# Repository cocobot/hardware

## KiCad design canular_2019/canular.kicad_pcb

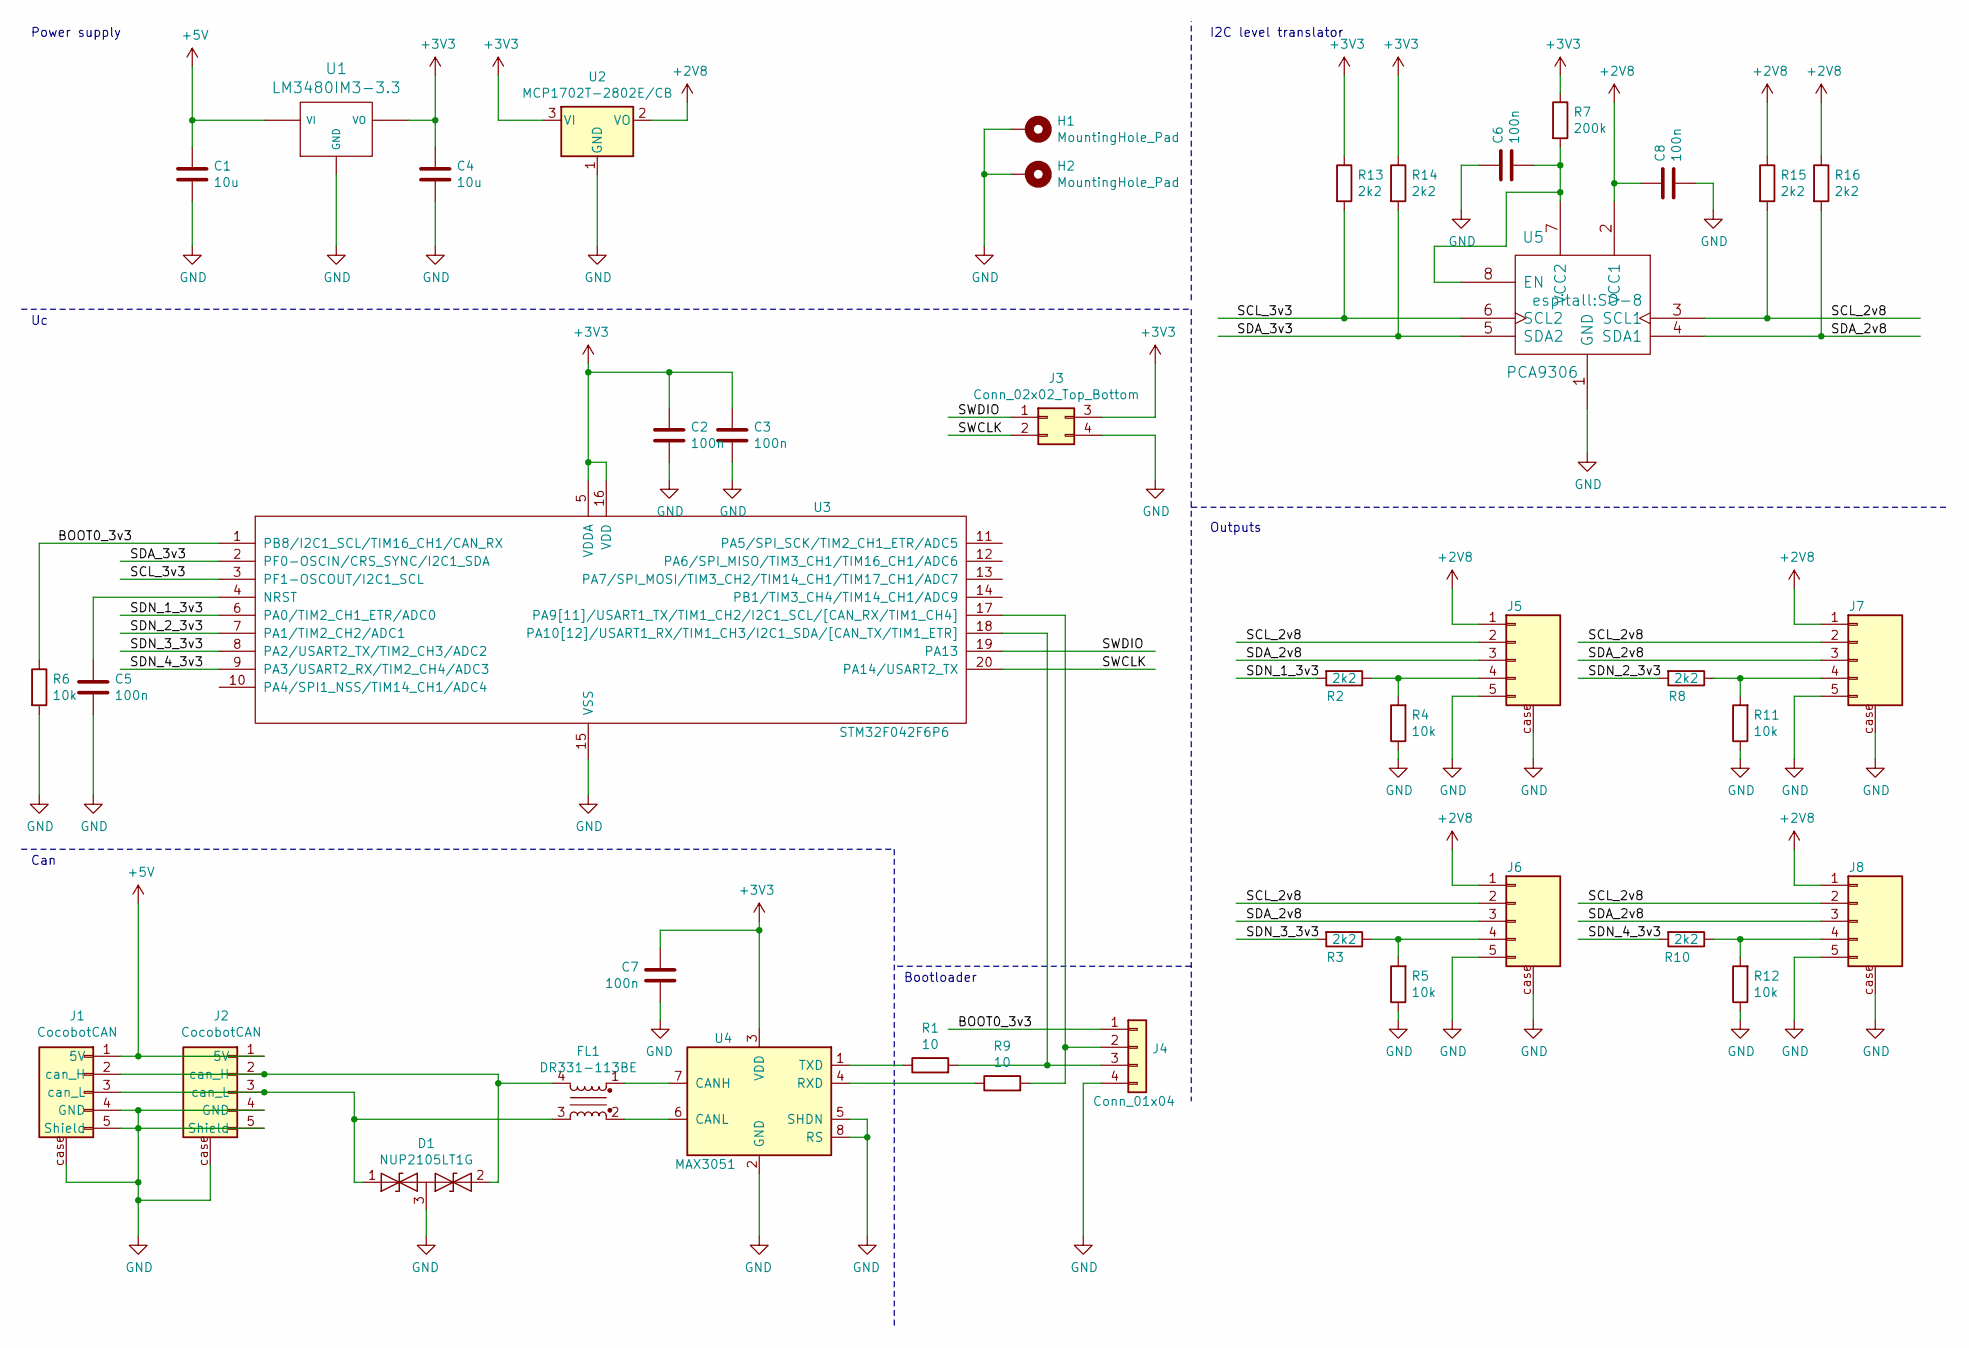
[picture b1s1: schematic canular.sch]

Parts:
C1, C4: 10u; C_0805
C2, C3, C5, C6, C7, C8: 100n; C_0603
D1: NUP2105LT1G; SOT-23
FL1: DR331-113BE; DR331
H1, H2: MountingHole_Pad; MountingHole_3.2mm_M3_Pad
J1, J2: CocobotCAN; JST_PH_S5B-PH-SM4-TB_05x2.00mm_Angled
J3: Conn_02x02_Top_Bottom; PinHeader_2x02_P2.54mm_Vertical
J4: Conn_01x04; PinHeader_1x04_P2.54mm_Vertical
J5, J6, J7, J8: JST_PH_S5B-PH-SM4-TB_05x2.00mm_Angled
R1, R9: 10; R_0603
R2, R3, R8, R10, R13, R14, R15, R16: 2k2; R_0603
R4, R5, R6, R11, R12: 10k; R_0603
R7: 200k; R_0603
U1: LM3480IM3-3.3; SOT-23
U2: MCP1702T-2802E/CB; SOT-23
U3: STM32F042F6P6; TSSOP-20_4.4x6.5mm_Pitch0.65mm
U4: MAX3051; SOIC-8_3.9x4.9mm_P1.27mm
U5: PCA9306; SO-8

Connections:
+2V8: C8.1, J5.1, J6.1, J7.1, J8.1, R15.1, R16.1, U2.2 (VO), U5.2 (VCC1)
+3V3: C2.1, C3.1, C4.1, C7.1, J3.3, R7.1, R13.1, R14.1, U1.1 (VO), U2.3 (VI), U3.5 (VDDA), U3.16 (VDD), U4.3 (VDD)
+5V: C1.1, J1.1 (5V), J2.1 (5V), U1.2 (VI)
/BOOT0_3v3: J4.1, R6.1, U3.1 (PB8/I2C1_SCL/TIM16_CH1/CAN_RX)
/SCL_2v8: J5.2, J6.2, J7.2, J8.2, R15.2, U5.3 (SCL1)
/SCL_3v3: R13.2, U3.3 (PF1-OSCOUT/I2C1_SCL), U5.6 (SCL2)
/SDA_2v8: J5.3, J6.3, J7.3, J8.3, R16.2, U5.4 (SDA1)
/SDA_3v3: R14.2, U3.2 (PF0-OSCIN/CRS_SYNC/I2C1_SDA), U5.5 (SDA2)
/SDN_1_3v3: R2.2, U3.6 (PA0/TIM2_CH1_ETR/ADC0)
/SDN_2_3v3: R8.2, U3.7 (PA1/TIM2_CH2/ADC1)
/SDN_3_3v3: R3.2, U3.8 (PA2/USART2_TX/TIM2_CH3/ADC2)
/SDN_4_3v3: R10.2, U3.9 (PA3/USART2_RX/TIM2_CH4/ADC3)
/SWCLK: J3.2, U3.20 (PA14/USART2_TX)
/SWDIO: J3.1, U3.19 (PA13)
GND: C1.2, C2.2, C3.2, C4.2, C5.2, C6.1, C7.2, C8.2, D1.3 (common), H1.1, H2.1, J1.4 (GND), J1.5 (Shield), J1.case, J2.4 (GND), J2.5 (Shield), J2.case, J3.4, J4.4, J5.5, J5.case, J6.5, J6.case, J7.5, J7.case, J8.5, J8.case, R4.1, R5.1, R6.2, R11.1, R12.1, U1.3 (GND), U2.1 (GND), U3.15 (VSS), U4.2 (GND), U4.5 (SHDN), U4.8 (RS), U5.1 (GND)
unnamed: C5.1, U3.4 (NRST)
unnamed: C6.2, R7.2, U5.7 (VCC2), U5.8 (EN)
unnamed: D1.1 (A1), FL1.3, J1.3 (can_L), J2.3 (can_L)
unnamed: D1.2 (A2), FL1.4, J1.2 (can_H), J2.2 (can_H)
unnamed: FL1.1, U4.7 (CANH)
unnamed: FL1.2, U4.6 (CANL)
unnamed: J4.2, R9.2, U3.17 (PA9[11]/USART1_TX/TIM1_CH2/I2C1_SCL/[CA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)
unnamed: J4.3, R1.2, U3.18 (PA10[12]/USART1_RX/TIM1_CH3/I2C1_SDA/[C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)
unnamed: J5.4, R2.1, R4.2
unnamed: J6.4, R3.1, R5.2
unnamed: J7.4, R8.1, R11.2
unnamed: J8.4, R10.1, R12.2
unnamed: R1.1, U4.1 (TXD)
unnamed: R9.1, U4.4 (RXD)

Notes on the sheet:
Power supply
Can
Bootloader
I2C level translator
Outputs

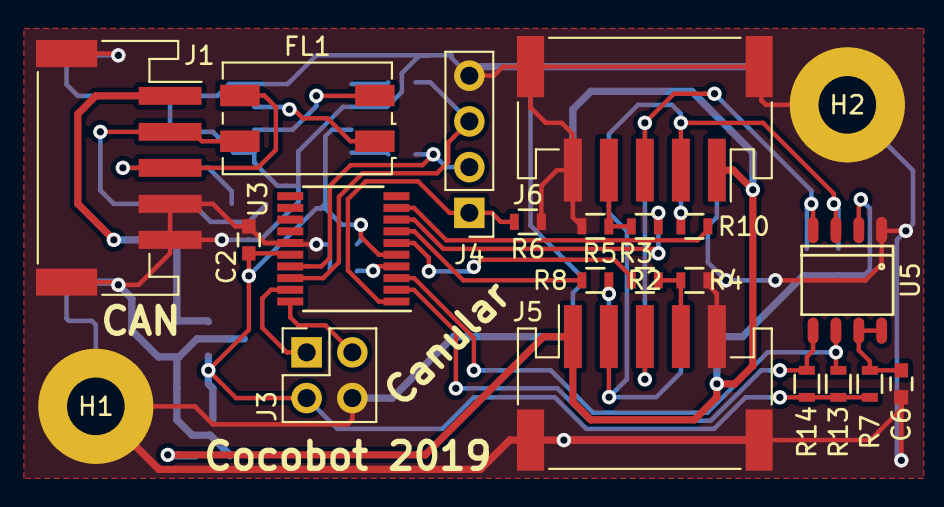
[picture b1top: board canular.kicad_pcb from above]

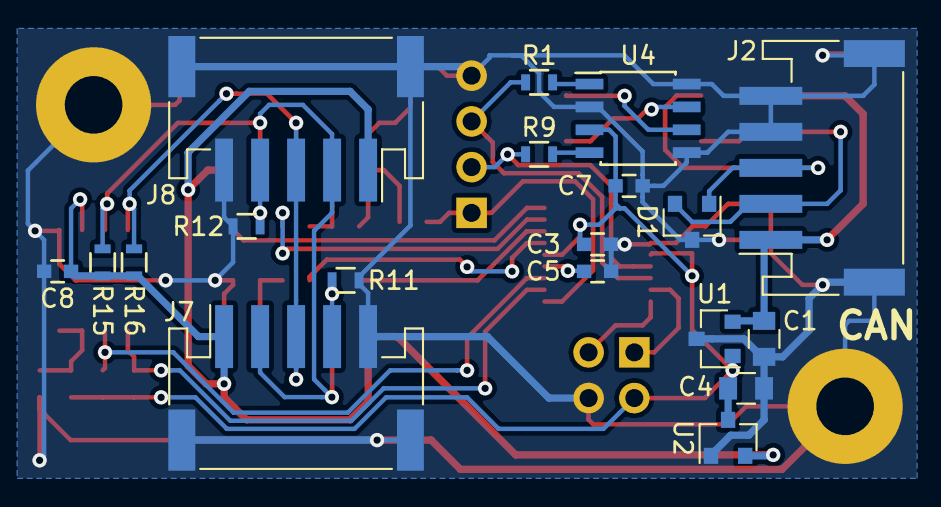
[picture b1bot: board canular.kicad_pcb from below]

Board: 2 copper layers, 41 parts (19 on the bottom side), 29 nets.

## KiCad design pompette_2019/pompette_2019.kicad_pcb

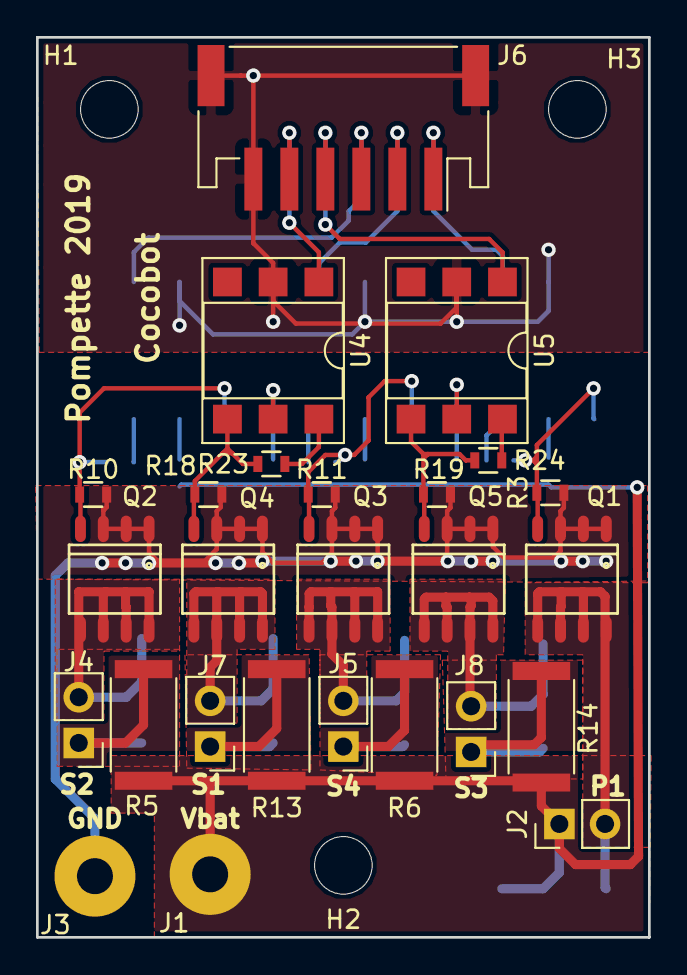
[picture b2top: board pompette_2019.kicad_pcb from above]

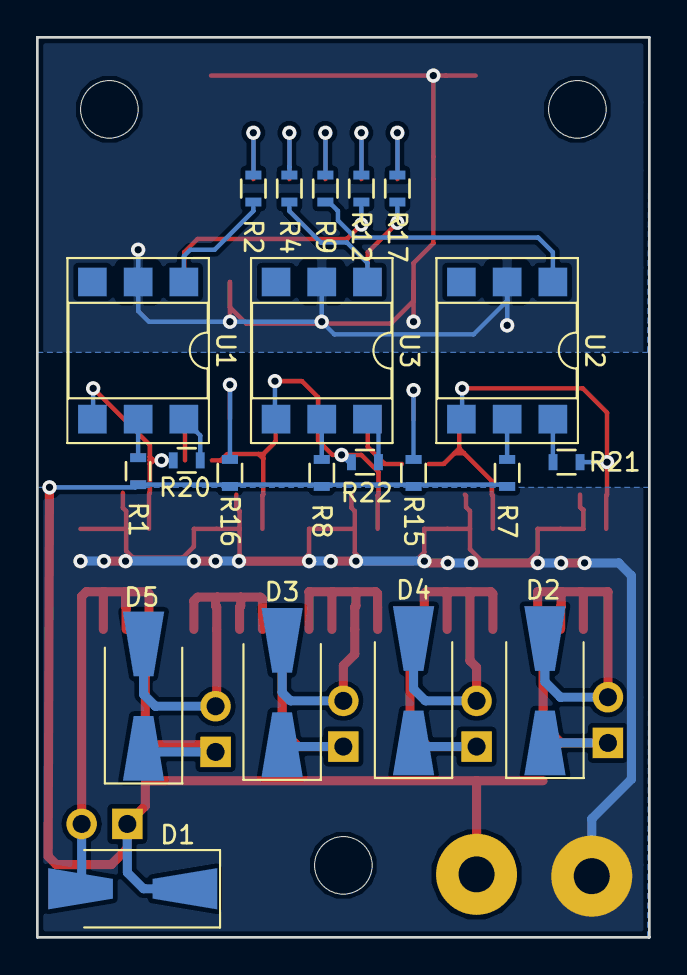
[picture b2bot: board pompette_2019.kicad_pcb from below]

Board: 2 copper layers, 34.0 x 50.0 mm, 50 parts (21 on the bottom side), 37 nets.

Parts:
D1, D2, D3, D4, D5: SS24; D_SMA-SMB_Universal_Handsoldering
H1, H2, H3: Conn_01x01; MountingHole_3.2mm_M3
J1, J3: Conn_01x01; SolderWirePad_single_2mmDrill
J2, J4, J5, J7, J8: Conn_01x02; Pin_Header_Straight_1x02_Pitch2.54mm
J6: JST_PH_S6B-PH-SM4-TB_06x2.00mm_Angled
Q1, Q2, Q3, Q4, Q5: DMG4466SSS-13
R1, R7, R8, R15, R16: 1k; R_0603
R2, R4, R9, R12, R17: 220; R_0603
R3, R10, R11, R18, R19: 10k; R_0603
R5, R6, R13, R14: R; R_2512
R20, R21, R22, R23, R24: 470k; R_0603
U1, U2, U3, U4, U5: CNY17-3-300E; DIP-6_W7.62mm_SMDSocket_SmallPads

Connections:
+BATT: D1.1, J1.1, J2.1, R1.1, R5.1, R6.1, R7.1, R8.1, R13.1, R14.1, R15.1, R16.1
/pump_3v3: J6.1, R2.2
/solenoid_1_3v3: J6.2, R4.2
/solenoid_2_3v3: J6.3, R9.2
/solenoid_3_3v3: J6.4, R12.2
/solenoid_4_3v3: J6.5, R17.2
GND: J3.1, Q1.S, Q2.S, Q3.S, Q4.S, Q5.S, R3.2, R10.2, R11.2, R18.2, R19.2
GNDD: J6.6, J6.case, U1.2, U2.2, U3.2, U4.2, U5.2
unnamed: D1.2, J2.2, Q1.D
unnamed: D2.1, J4.1, R5.2
unnamed: D2.2, J4.2, Q2.D
unnamed: D3.1, J5.1, R6.2
unnamed: D3.2, J5.2, Q3.D
unnamed: D4.1, J7.1, R13.2
unnamed: D4.2, J7.2, Q4.D
unnamed: D5.1, J8.1, R14.2
unnamed: D5.2, J8.2, Q5.D
unnamed: Q1.G, R3.1, R20.1, U1.4
unnamed: Q2.G, R10.1, R21.1, U2.4
unnamed: Q3.G, R11.1, R22.1, U3.4
unnamed: Q4.G, R18.1, R23.1, U4.4
unnamed: Q5.G, R19.1, R24.1, U5.4
unnamed: R1.2, U1.5
unnamed: R2.1, U1.1
unnamed: R4.1, U3.1
unnamed: R7.2, U2.5
unnamed: R8.2, U3.5
unnamed: R9.1, U2.1
unnamed: R12.1, U5.1
unnamed: R15.2, U4.5
unnamed: R16.2, U5.5
unnamed: R17.1, U4.1
unnamed: R20.2, U1.6
unnamed: R21.2, U2.6
unnamed: R22.2, U3.6
unnamed: R23.2, U4.6
unnamed: R24.2, U5.6

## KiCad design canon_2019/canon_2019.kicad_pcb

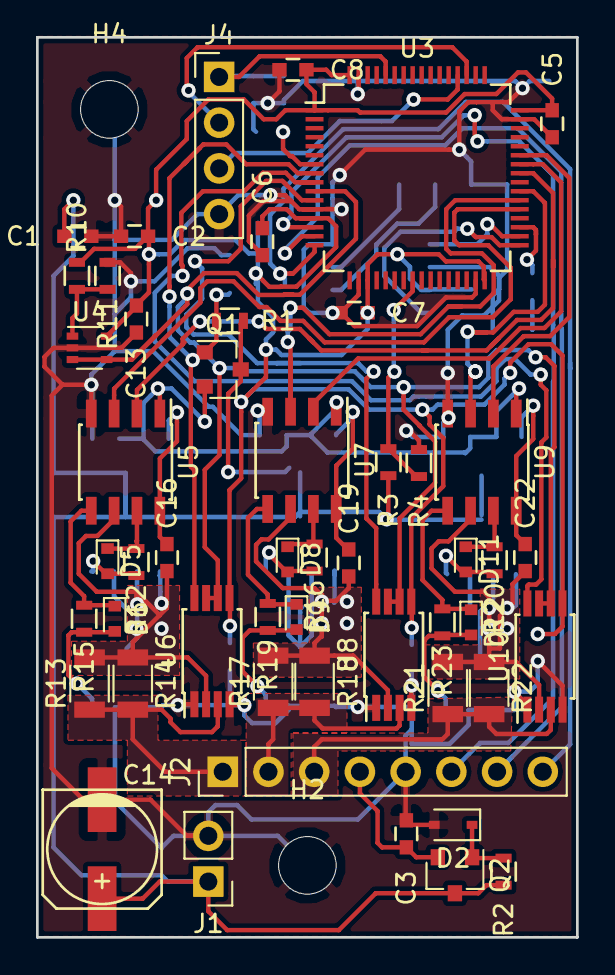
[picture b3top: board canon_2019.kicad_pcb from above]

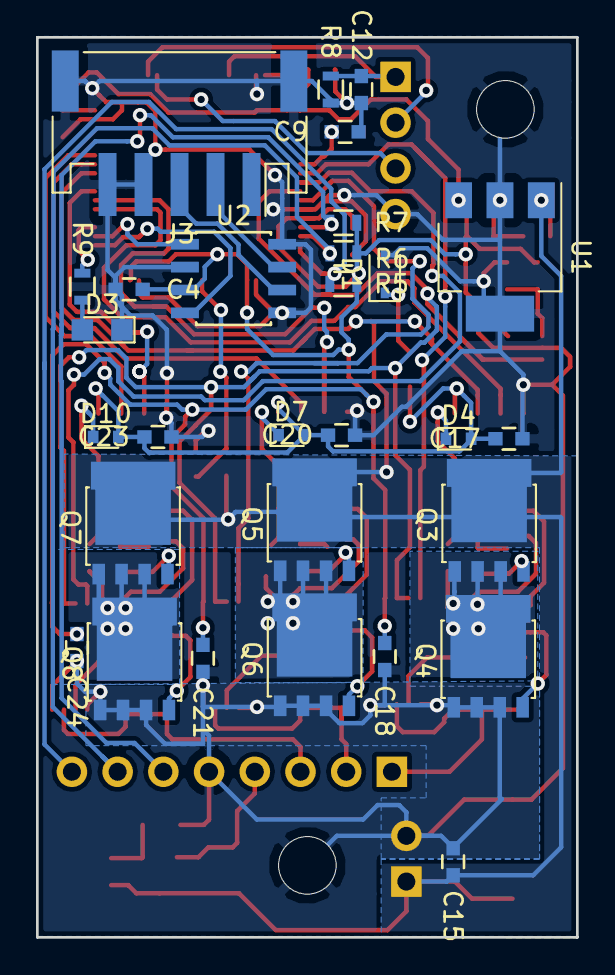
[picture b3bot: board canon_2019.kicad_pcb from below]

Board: 2 copper layers, 30.0 x 50.0 mm, 81 parts (29 on the bottom side), 53 nets.

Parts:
C1, C4, C5, C6, C7, C8, C9, C12, C13, C16, C17, C18, C19, C20, C21, C22, C23, C24: 100n; C_0603
C2, C3: 470n; C_0603
C14: CP; c_elec_6.3x7.7
C15: 2u2; C_0603
D1: BZD27Cxx/15V; D_SOD-323
D2: BZD27Cxx/5V6; D_SOD-323
D3: LED; LED_0805
D4, D5, D6, D7, D8, D9, D10, D11, D12: BAS-40-02V-V-G-08; D_SOD-523
H2, H4: MountingHole_Pad; MountingHole_3.2mm_M3
J1: Conn_01x02; Pin_Header_Straight_1x02_Pitch2.54mm
J2: Conn_01x08; Pin_Header_Straight_1x08_Pitch2.54mm
J3: CocobotCAN; JST_PH_S5B-PH-SM4-TB_05x2.00mm_Angled
J4: Conn_01x04; Pin_Header_Straight_1x04_Pitch2.54mm
Q1: BSS126; SOT-23
Q2: SO2222A; SOT-23
Q3, Q4, Q5, Q6, Q7, Q8: Q_NMOS_LFPAK; SOT-669_LFPAK
R1, R2, R3, R5, R6, R7, R8, R10, R11: 10k; R_0603
R4, R9: 1k; R_0603
R12, R15, R16, R19, R20, R23: 47; R_0603
R13, R14, R17, R18, R21, R22: 5m; R_1206
U1: LM3940IMP-3.3; SOT-223-3_TabPin2
U2: MAX3051; SOIC-8_3.9x4.9mm_Pitch1.27mm
U3: STM32L496RGTx; LQFP-64_10x10mm_Pitch0.5mm
U4: OPA349SA-3K; SOT-353_SC-70-5
U5, U7, U9: IR2104; SOIC-8_3.9x4.9mm_Pitch1.27mm
U6, U8, U10: INA240A1PW; TSSOP-8_4.4x3mm_Pitch0.65mm

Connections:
+3V3: C2.1, C4.1, C5.1, C6.1, C7.1, C8.1, C13.2, C18.2, C21.2, C24.2, R5.1, R6.1, R7.1, R10.1, U1.3, U2.3, U3.1, U3.13, U3.19, U3.32, U3.48, U3.64, U4.5, U6.5, U8.5, U10.5
/Control/BAT_ADC_0-3v3: R3.2, R4.1, U3.24
/Control/HALL_U_3v3: J2.6, R7.2, U3.14
/Control/HALL_V_3v3: J2.7, R6.2, U3.15
/Control/HALL_W_3v3: J2.8, R5.2, U3.16
/Control/I_U_0-3v3: U3.8, U6.8
/Control/I_V_0-3v3: U3.11, U8.8
/Control/I_W_0-3v3: U3.9, U10.8
/Control/REF_1v65: U3.10, U4.3, U4.4, U6.6, U6.7, U8.6, U8.7, U10.6, U10.7
/Control/UEN_3v3: U3.37, U5.3
/Control/UPWM_3v3: U3.41, U5.2
/Control/VEN_3v3: U3.38, U7.3
/Control/VPWM_3v3: U3.42, U7.2
/Control/WEN_3v3: U3.39, U9.3
/Control/WPWM_3v3: U3.43, U9.2
/Control/boot0_3v3: C12.1, J4.1, R8.1, U3.60
/Control/can_rx: U2.4, U3.33
/Control/can_tx: U2.1, U3.34
/Control/rx_3v3: J4.3, U3.52
/Control/tx_3v3: J4.2, U3.51
/Drive/U_PH: J2.1, R13.1, R14.2, U6.3
/Drive/V_PH: J2.2, R17.1, R18.2, U8.3
/Drive/Vdrv: C17.1, C20.1, C23.1, D4.2, D7.2, D10.2, Q1.2, U5.1, U7.1, U9.1
/Drive/W_PH: J2.3, R21.1, R22.2, U10.3
/PWR_BAT: C1.1, C14.1, C15.1, J1.1, Q1.3, Q2.3, Q3.5, Q5.5, Q7.5, R1.1, R2.1, R3.1, U1.1
GND: C1.2, C2.2, C3.2, C4.2, C5.2, C6.2, C7.2, C8.2, C9.2, C12.2, C13.1, C14.2, C15.2, C17.2, C18.1, C20.2, C21.1, C23.2, C24.1, D1.2, D2.2, D3.1, H2.1, H4.1, J1.2, J2.5, J3.4, J3.5, J3.case, J4.4, Q4.1, Q4.2, Q4.3, Q6.1, Q6.2, Q6.3, Q8.1, Q8.2, Q8.3, R4.2, R8.2, R11.2, U1.2, U2.2, U2.5, U2.8, U3.12, U3.18, U3.31, U3.47, U3.63, U4.2, U5.4, U6.1, U6.4, U7.4, U8.1, U8.4, U9.4, U10.1, U10.4
unnamed: C3.1, J2.4, Q2.2
unnamed: C9.1, U3.7
unnamed: C16.1, D4.1, U5.8
unnamed: C16.2, Q3.1, Q3.2, Q3.3, Q4.5, R13.2, R14.1, U5.6, U6.2
unnamed: C19.1, D7.1, U7.8
unnamed: C19.2, Q5.1, Q5.2, Q5.3, Q6.5, R17.2, R18.1, U7.6, U8.2
unnamed: C22.1, D10.1, U9.8
unnamed: C22.2, Q7.1, Q7.2, Q7.3, Q8.5, R21.2, R22.1, U9.6, U10.2
unnamed: D1.1, Q1.1, R1.2
unnamed: D2.1, Q2.1, R2.2
unnamed: D3.2, R9.2
unnamed: D5.1, R12.2, U5.7
unnamed: D5.2, Q3.4, R12.1
unnamed: D6.1, R15.2, U5.5
unnamed: D6.2, Q4.4, R15.1
unnamed: D8.1, R16.2, U7.7
unnamed: D8.2, Q5.4, R16.1
unnamed: D9.1, R19.2, U7.5
unnamed: D9.2, Q6.4, R19.1
unnamed: D11.1, R20.2, U9.7
unnamed: D11.2, Q7.4, R20.1
unnamed: D12.1, R23.2, U9.5
unnamed: D12.2, Q8.4, R23.1
unnamed: J3.2, U2.7
unnamed: J3.3, U2.6
unnamed: R9.1, U3.35
unnamed: R10.2, R11.1, U4.1

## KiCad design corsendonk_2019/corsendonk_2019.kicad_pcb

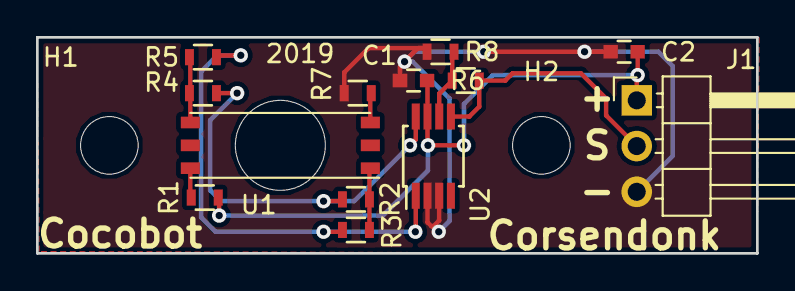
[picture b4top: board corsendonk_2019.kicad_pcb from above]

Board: 2 copper layers, 40.0 x 12.0 mm, 15 parts (0 on the bottom side), 10 nets.

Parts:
C1: 100n; C_0603
C2: 2u2; C_0603
H1, H2: Conn_01x01; MountingHole_3.2mm_M3
J1: Conn_01x03; Pin_Header_Angled_1x03_Pitch2.54mm
R1, R2, R3, R4, R5, R6, R7, R8: R; R_0603
U1: 2SMPP-02
U2: AD628; MSOP-8_3x3mm_Pitch0.65mm

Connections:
+5V: C1.2, C2.1, J1.1, R1.1, U2.7
/pres_0-5v: J1.2, R6.2, U2.5
GND: C1.1, C2.2, J1.3, R7.2, R8.1, U2.2, U2.3
unnamed: R1.2, U1.6
unnamed: R2.1, R4.1, U2.8
unnamed: R2.2, R3.2, U1.1
unnamed: R3.1, R5.1, U2.1
unnamed: R4.2, R5.2, U1.4
unnamed: R6.1, R8.2, U2.6
unnamed: R7.1, U1.3

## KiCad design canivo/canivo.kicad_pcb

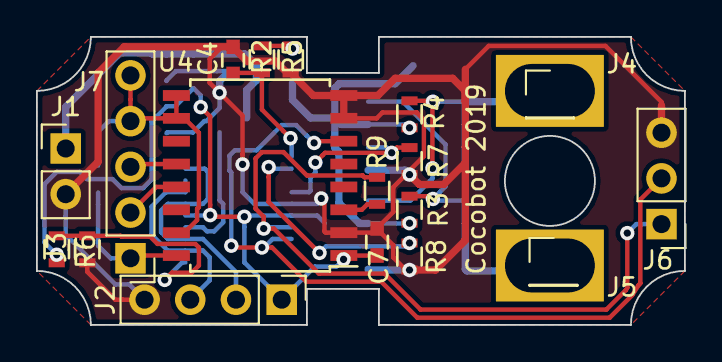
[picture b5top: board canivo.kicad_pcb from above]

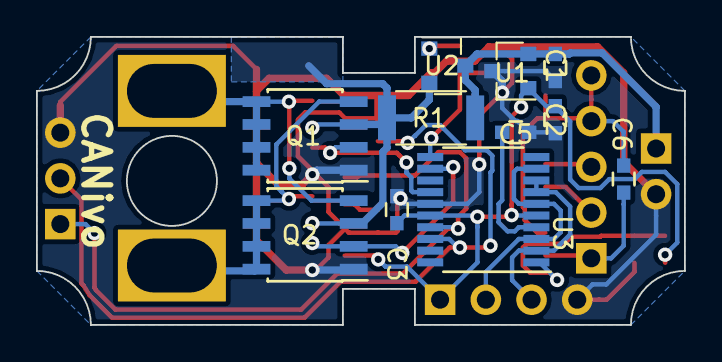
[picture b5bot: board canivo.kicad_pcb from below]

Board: 2 copper layers, 36.0 x 16.0 mm, 29 parts (11 on the bottom side), 21 nets.

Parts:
C1, C2, C3, C4, C5, C6, C7: 100n; C_0603
J1: Conn_01x02; Pin_Header_Straight_1x02_Pitch2.54mm
J2: Conn_01x04; Pin_Header_Straight_1x04_Pitch2.54mm
J3: Conn_01x02; R_0603
J4, J5: Conn_01x01; Pin_Header_Straight_1x01_Pitch2.54mm
J6: Conn_01x03; Pin_Header_Straight_1x03_Pitch2.54mm
J7: Conn_01x05; Pin_Header_Straight_1x05_Pitch2.54mm
Q1, Q2: DMC3025LSD; SOIC-8_3.9x4.9mm_Pitch1.27mm
R1: 0.05; R_2010
R2, R5: 1k; R_0603
R3, R4, R7, R8: 100k; R_0603
R6: 10k; R_0603
R9: 10; R_0603
U1: LM3480IM3-3.3; SOT-23
U2: ZXCT1009FTA; SOT-23
U3: STM32F042F6P6; TSSOP-20_4.4x6.5mm_Pitch0.65mm
U4: ISO1050DW; SOIC-16W_7.5x10.3mm_Pitch1.27mm

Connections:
+3V3: C2.1, C3.1, C7.1, J2.1, J3.1, U1.1, U3.5, U3.16, U4.1
+5P: C1.1, J1.1, R1.1, U1.2, U2.3
GND: C1.2, C2.2, C3.2, C4.2, C5.2, C7.2, J1.2, J2.4, J6.3, Q1.1, Q2.1, R5.2, R6.2, R7.2, R8.2, U1.3, U3.15, U4.2, U4.7, U4.8
unnamed: C4.1, R2.2, U3.11
unnamed: C5.1, U3.4
unnamed: C6.1, J7.1, U4.16
unnamed: C6.2, J7.4, J7.5, U4.9, U4.10, U4.15
unnamed: Q1.3, Q2.3, R1.2, R3.1, R4.1, U2.2
unnamed: J4.1, Q1.5, Q1.6, Q1.7, Q1.8, Q2.4, R4.2
unnamed: J5.1, Q1.4, Q2.5, Q2.6, Q2.7, Q2.8, R3.2
unnamed: J2.2, U3.3, U3.6, U3.9
unnamed: J2.3, U3.2, U3.7, U3.8
unnamed: J3.2, R6.1, U3.1
unnamed: J6.1, R9.2, U3.17
unnamed: J6.2, U3.18, U4.6
unnamed: J7.2, U4.13
unnamed: J7.3, U4.12
unnamed: Q1.2, R7.1, U3.14
unnamed: Q2.2, R8.1, U3.12
unnamed: R2.1, R5.1, U2.1
unnamed: R9.1, U4.3

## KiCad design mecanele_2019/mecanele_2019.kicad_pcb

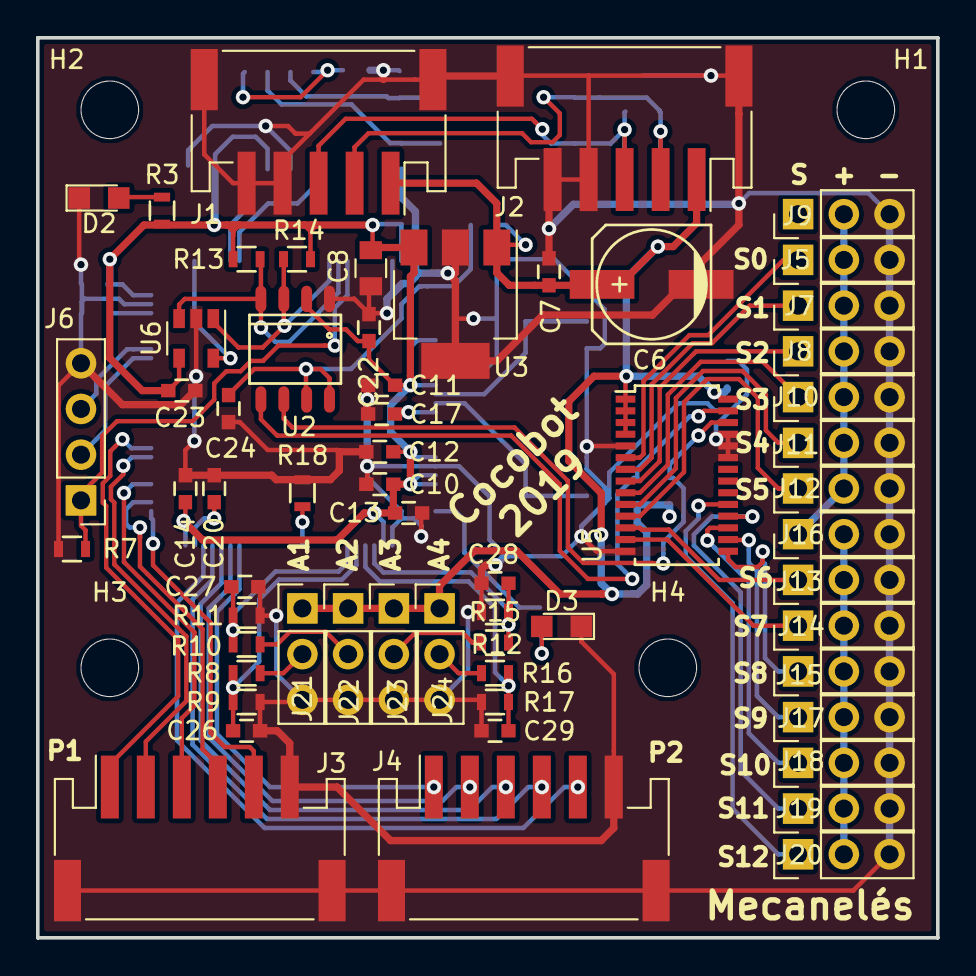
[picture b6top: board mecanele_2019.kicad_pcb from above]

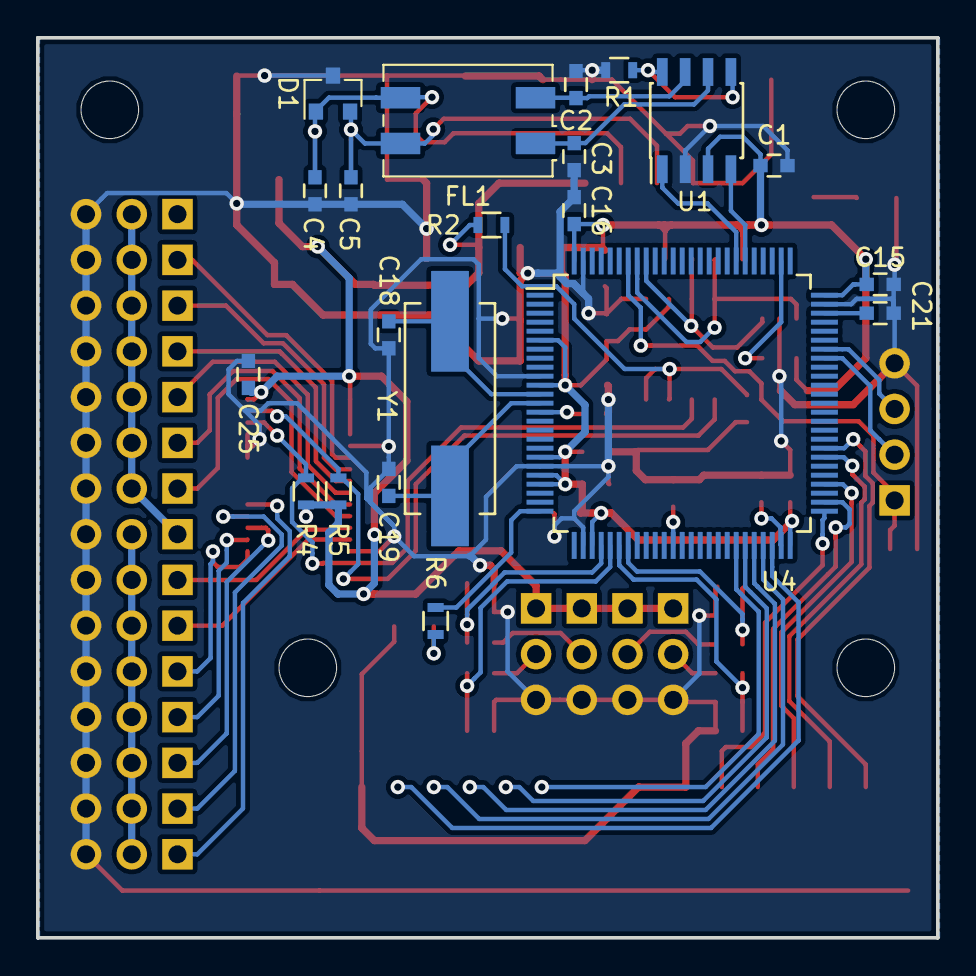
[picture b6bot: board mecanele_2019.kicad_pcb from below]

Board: 2 copper layers, 50.0 x 50.0 mm, 85 parts (21 on the bottom side), 61 nets.

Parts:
C1, C10, C11, C12, C13, C14, C15, C16, C17, C22, C23, C24, C25, C26, C27, C28, C29: 100n; C_0603
C2, C3, C4, C5: C; C_0603
C6: CP; c_elec_6.3x7.7
C7, C20, C21: 2u2; C_0603
C8: 47u; C_0805
C18, C19: 20p; C_0603
D1: NUP2105LT1G; SOT-23
D2, D3: LED; LED_0805
FL1: DR331-113BE; DR331
H1, H2, H3, H4: Conn_01x01; MountingHole_3.2mm_M3
J1, J2: CocobotCAN; JST_PH_S5B-PH-SM4-TB_05x2.00mm_Angled
J3, J4: JST_PH_S6B-PH-SM4-TB_06x2.00mm_Angled
J5, J7, J8, J9, J10, J11, J12, J13, J14, J15, J16, J17, J18, J19, J20, J21, J22, J23, J24: Conn_01x03; Pin_Header_Straight_1x03_Pitch2.54mm
J6: Conn_01x04; Socket_Strip_Straight_1x04_Pitch2.54mm
R1: 0; R_0603
R2: 200k; R_0603
R3, R6: 220; R_0603
R4, R5, R13, R14: 2k2; R_0603
R7, R18: 10k; R_0603
R8, R9, R10, R11, R12, R15, R16, R17: R; R_0603
U1: MAX3051ESA; SOIC-8_3.9x4.9mm_Pitch1.27mm
U2: PCA9306; SO-8
U3: LM3940IMP-3.3; SOT-223-3_TabPin2
U4: STM32F407VG; LQFP-100_14x14mm_Pitch0.5mm
U5: PCA9685; TSSOP-28_4.4x9.7mm_Pitch0.65mm
U6: 24LC64T-I; SOT-23-5
Y1: 8M; Crystal_HC49-SD_SMD

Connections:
+3V3: C1.1, C8.1, C10.1, C11.1, C12.1, C13.1, C14.1, C15.1, C16.1, C22.1, C23.1, R3.1, R13.1, R14.1, U1.3, U2.2, U3.3, U4.6, U4.11, U4.19, U4.21, U4.22, U4.28, U4.50, U4.75, U4.100, U6.4
+5V: C6.1, C7.1, C25.1, J1.1, J2.1, J21.1, J22.1, J23.1, J24.1, R2.1, R4.1, R5.1, U3.1, U5.1, U5.2, U5.3, U5.4, U5.28
/CAN/can_rx_3v3: U1.4, U4.81
/CAN/can_tx_3v3: U1.1, U4.82
/Sensor/ana_1_0-3v3: C26.1, R8.2, R9.2, U4.31
/Sensor/ana_2_0-3v3: C27.1, R10.2, R11.2, U4.32
/Sensor/ana_3_0-3v3: C28.1, R12.2, R15.2, U4.29
/Sensor/ana_4_0-3v3: C29.1, R16.2, R17.2, U4.30
/Servo/S0: J5.1, U5.6
/Servo/S1: J7.1, U5.7
/Servo/S2: J8.1, U5.8
/Servo/S3: J10.1, U5.9
/Servo/S4: J11.1, U5.10
/Servo/S5: J12.1, U5.11
/Servo/S6: J13.1, U5.12
/Servo/S7: J14.1, U5.13
/Servo/S8: J15.1, U5.15
/Servo/S9: J17.1, U5.16
/Servo/S10: J18.1, U5.17
/Servo/S11: J19.1, U5.18
/Servo/S12: J20.1, U5.19
/Servo/scl_3v3: R14.2, U2.3, U4.92, U6.1
/Servo/sda_3v3: R13.2, U2.4, U4.93, U6.3
/uc/BOOT0_3v3: J6.1, R7.1, U4.94
/uc/BOOT1_3v3: R18.1, U4.37
/uc/nSRST_3v3: C17.1, U4.14
/uc/pump_1_3v3: J3.1, U4.58
/uc/pump_2_3v3: J4.1, U4.44
/uc/solenoid_1_3v3: J3.2, U4.57
/uc/solenoid_2_3v3: J3.3, U4.54
/uc/solenoid_3_3v3: J3.4, U4.52
/uc/solenoid_4_3v3: J3.5, U4.51
/uc/solenoid_5_3v3: J4.2, U4.45
/uc/solenoid_6_3v3: J4.3, U4.46
/uc/solenoid_7_3v3: J4.4, U4.47
/uc/solenoid_8_3v3: J4.5, U4.48
GND: C1.2, C2.2, C3.2, C4.2, C5.2, C6.2, C7.2, C8.2, C10.2, C11.2, C12.2, C13.2, C14.2, C15.2, C16.2, C17.2, C18.2, C19.2, C20.2, C21.2, C22.2, C23.2, C24.2, C25.2, C26.2, C27.2, C28.2, C29.2, D1.3, D2.1, D3.1, J1.4, J1.5, J1.case, J2.4, J2.5, J2.case, J3.6, J3.case, J4.6, J4.case, J5.3, J6.4, J7.3, J8.3, J9.3, J10.3, J11.3, J12.3, J13.3, J14.3, J15.3, J16.3, J17.3, J18.3, J19.3, J20.3, J21.3, J22.3, J23.3, J24.3, R1.2, R7.2, R9.1, R11.1, R15.1, R17.1, R18.2, U1.2, U2.1, U3.2, U4.10, U4.20, U4.27, U4.74, U4.99, U5.5, U5.14, U5.23, U5.24, U5.25, U6.2
unnamed: C2.1, FL1.2, U1.7
unnamed: C3.1, FL1.1, U1.6
unnamed: C4.1, D1.1, FL1.3, J1.2, J2.2
unnamed: C5.1, D1.2, FL1.4, J1.3, J2.3
unnamed: C18.1, U4.12, Y1.1
unnamed: C19.1, U4.13, Y1.2
unnamed: C20.1, U4.49
unnamed: C21.1, U4.73
unnamed: C24.1, R2.2, U2.7, U2.8
unnamed: D2.2, R3.2
unnamed: D3.2, R6.2
unnamed: J6.2, U4.68
unnamed: J6.3, U4.69
unnamed: J5.2, J7.2, J8.2, J9.2, J10.2, J11.2, J12.2, J16.1
unnamed: J13.2, J14.2, J15.2, J16.2, J17.2, J18.2, J19.2, J20.2
unnamed: J21.2, R8.1
unnamed: J22.2, R10.1
unnamed: J23.2, R12.1
unnamed: J24.2, R16.1
unnamed: R1.1, U1.5, U1.8
unnamed: R4.2, U2.6, U5.26
unnamed: R5.2, U2.5, U5.27
unnamed: R6.1, U4.25
unnamed: U4.77, U6.5

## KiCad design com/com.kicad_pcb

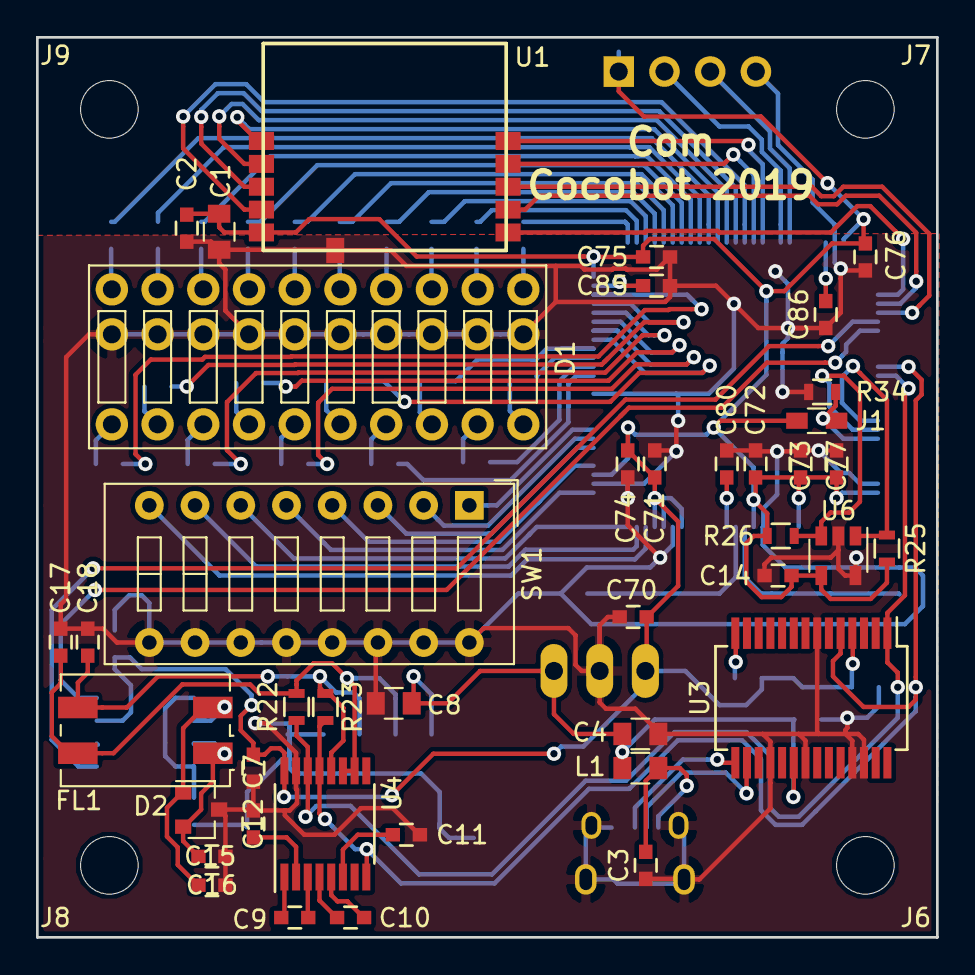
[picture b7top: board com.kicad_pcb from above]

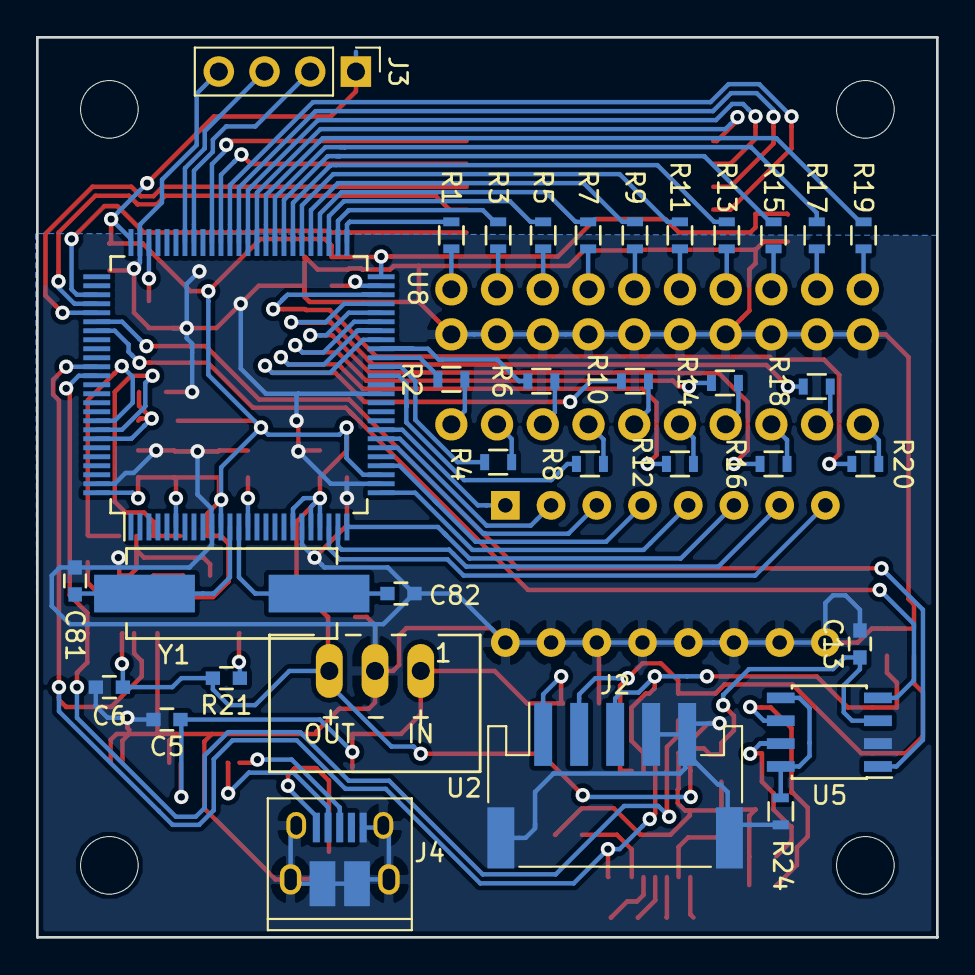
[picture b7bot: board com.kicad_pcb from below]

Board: 2 copper layers, 50.0 x 50.0 mm, 79 parts (34 on the bottom side), 89 nets.

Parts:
C1, C8: 10u; C_0805
C2, C5, C6, C7, C9, C10, C11, C12, C13, C14, C71, C72, C73, C74, C75, C76, C77, C80: 100n; C_0603
C3: 10n; C_0603
C4: 4u7; C_0805
C15, C16, C17, C18: C; C_0603
C70: 10u; C_0603
C81, C82: 20p; C_0603
C85, C86: 2u2; C_0603
D1: XGURUGX10D
D2: NUP2105LT1G; SOT-23
FL1: DR331-113BE; DR331
J1: Conn_01x02; R_0603_HandSoldering
J2: CocobotCAN; JST_PH_S5B-PH-SM4-TB_05x2.00mm_Angled
J3: Conn_01x04; Socket_Strip_Straight_1x04_Pitch2.54mm
J4: USB_B_Micro; USB_Micro-B_10103594-0001LF
J6, J7, J8, J9: Conn_01x01; MountingHole_3.2mm_M3
L1: Ferrite_Bead; C_0805
R1, R2, R3, R4, R5, R6, R7, R8, R9, R10, R11, R12, R13, R14, R15, R16, R17, R18, R19, R20: 220; R_0603
R21: 10k; C_0603
R22, R23, R24: 0; R_0603
R25, R26: 2k2; R_0603
R34: 10k; R_0603
SW1: SW_DIP_x08; SW_DIP_x8_W7.62mm_Slide
U1: SPSGRF-868
U2: TSR1-2433; TSR-1
U3: FT232RL; SSOP-28_5.3x10.2mm_Pitch0.65mm
U4: MAX3232CPW; TSSOP-16_4.4x5mm_Pitch0.65mm
U5: MAX3051ESA; SOIC-8_3.9x4.9mm_Pitch1.27mm
U6: 24LC64T-I; SOT-23-5
U8: STM32F407VG; LQFP-100_14x14mm_Pitch0.5mm
Y1: 8M; Crystal_HC49-SD_SMD

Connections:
+3V3: C1.1, C2.1, C6.1, C7.2, C13.1, C14.1, C70.1, C71.1, C72.1, C73.1, C74.1, C75.1, C76.1, C77.1, J1.1, J3.1, R21.1, R25.1, R26.1, U1.5, U2.3, U3.4, U4.16, U5.3, U6.4, U8.6, U8.11, U8.19, U8.21, U8.22, U8.28, U8.50, U8.75, U8.100
/CAN/can_h: C17.1, FL1.4, J2.2, R22.1, U4.10, U4.11
/CAN/can_l: C18.1, FL1.3, J2.3, R23.1, U4.12
/CAN/can_rx_3v3: U5.4, U8.82
/CAN/can_tx_3v3: U5.1, U8.81
/Computer/5v: C4.1, C5.1, C8.1, J2.1, L1.1, U2.1, U3.20
/Computer/rx_3v3: R22.2, U3.1, U4.14, U8.87
/Computer/tx_3v3: R23.2, U3.5, U4.8, U4.13, U8.86
/uc/BOOT0_3v3: J1.2, R34.1, U8.94
/uc/led_c1_1_3v3: R1.1, U8.51
/uc/led_c1_2_3v3: R3.1, U8.52
/uc/led_c1_3_3v3: R5.1, U8.53
/uc/led_c1_4_3v3: R7.1, U8.54
/uc/led_c1_5_3v3: R9.1, U8.55
/uc/led_c1_6_3v3: R11.1, U8.56
/uc/led_c1_7_3v3: R13.1, U8.57
/uc/led_c1_8_3v3: R15.1, U8.58
/uc/led_c1_9_3v3: R17.1, U8.59
/uc/led_c1_10_3v3: R19.1, U8.60
/uc/led_c2_1_3v3: R2.1, U8.41
/uc/led_c2_2_3v3: R4.1, U8.40
/uc/led_c2_3_3v3: R6.1, U8.42
/uc/led_c2_4_3v3: R8.1, U8.39
/uc/led_c2_5_3v3: R10.1, U8.43
/uc/led_c2_6_3v3: R12.1, U8.44
/uc/led_c2_7_3v3: R14.1, U8.45
/uc/led_c2_8_3v3: R16.1, U8.46
/uc/led_c2_9_3v3: R18.1, U8.47
/uc/led_c2_10_3v3: R20.1, U8.48
/uc/nSRST_3v3: C80.1, U8.14
/uc/rf_gpio0_3v3: U1.4, U8.64
/uc/rf_gpio1_3v3: U1.3, U8.63
/uc/rf_gpio2_3v3: U1.2, U8.62
/uc/rf_gpio3_3v3: U1.1, U8.61
/uc/rf_sdn_3v3: U1.11, U8.66
/uc/rf_spi_cs_3v3: U1.10, U8.65
/uc/rf_spi_miso_3v3: U1.8, U8.79
/uc/rf_spi_mosi_3v3: U1.9, U8.80
/uc/rf_spi_sck_3v3: U1.7, U8.78
/uc/sw1_3v3: SW1.1, U8.33
/uc/sw2_3v3: SW1.2, U8.32
/uc/sw3_3v3: SW1.3, U8.31
/uc/sw4_3v3: SW1.4, U8.29
/uc/sw5_3v3: SW1.5, U8.26
/uc/sw6_3v3: SW1.6, U8.25
/uc/sw7_3v3: SW1.7, U8.24
/uc/sw8_3v3: SW1.8, U8.23
GND: C1.2, C2.2, C3.2, C4.2, C5.2, C6.2, C7.1, C8.2, C11.2, C12.2, C13.2, C14.2, C15.2, C16.2, C17.2, C18.2, C70.2, C71.2, C72.2, C73.2, C74.2, C75.2, C76.2, C77.2, C80.2, C81.2, C82.2, C85.2, C86.2, D1.21, D1.22, D1.23, D1.24, D1.25, D1.26, D1.27, D1.28, D1.29, D1.30, D2.3, J2.4, J2.5, J2.case, J3.4, J4.5, J4.6, R24.2, R34.2, SW1.9, SW1.10, SW1.11, SW1.12, SW1.13, SW1.14, SW1.15, SW1.16, U1.6, U2.2, U3.7, U3.18, U3.21, U3.25, U3.26, U4.15, U5.2, U6.2, U6.5, U8.10, U8.20, U8.27, U8.37, U8.74, U8.99
unnamed: C3.1, J4.1, L1.2
unnamed: C9.1, U4.1
unnamed: C9.2, U4.3
unnamed: C10.1, U4.5
unnamed: C10.2, U4.4
unnamed: C11.1, U4.6
unnamed: C12.1, U4.2
unnamed: C15.1, D2.2, FL1.1, U5.7
unnamed: C16.1, D2.1, FL1.2, U5.6
unnamed: C81.1, U8.12, Y1.1
unnamed: C82.1, U8.13, Y1.2
unnamed: C85.1, U8.49
unnamed: C86.1, U8.73
unnamed: D1.1, R1.2
unnamed: D1.2, R3.2
unnamed: D1.3, R5.2
unnamed: D1.4, R7.2
unnamed: D1.5, R9.2
unnamed: D1.6, R11.2
unnamed: D1.7, R13.2
unnamed: D1.8, R15.2
unnamed: D1.9, R17.2
unnamed: D1.10, R19.2
unnamed: D1.11, R20.2
unnamed: D1.12, R18.2
unnamed: D1.13, R16.2
unnamed: D1.14, R14.2
unnamed: D1.15, R12.2
unnamed: D1.16, R10.2
unnamed: D1.17, R8.2
unnamed: D1.18, R6.2
unnamed: D1.19, R4.2
unnamed: D1.20, R2.2
unnamed: J3.2, U8.68
unnamed: J3.3, U8.69
unnamed: J4.2, U3.16
unnamed: J4.3, U3.15
unnamed: R21.2, U3.14
unnamed: R24.1, U5.5, U5.8
unnamed: R25.2, U6.1, U8.92
unnamed: R26.2, U6.3, U8.93

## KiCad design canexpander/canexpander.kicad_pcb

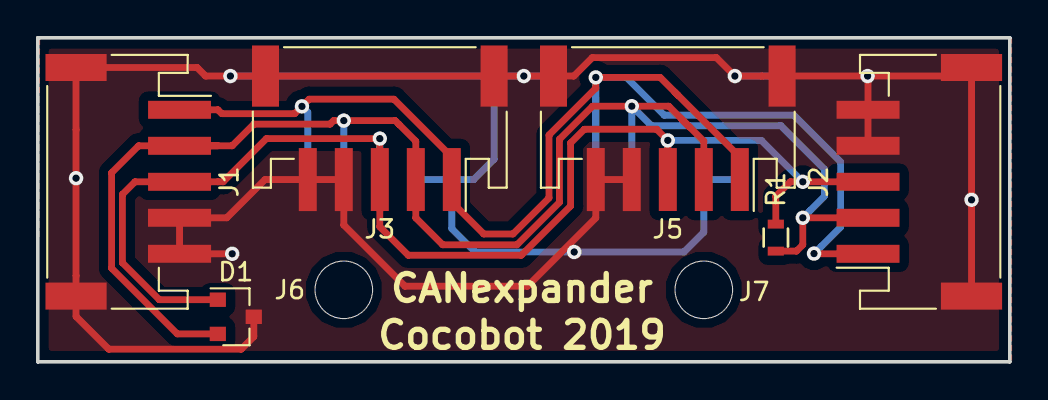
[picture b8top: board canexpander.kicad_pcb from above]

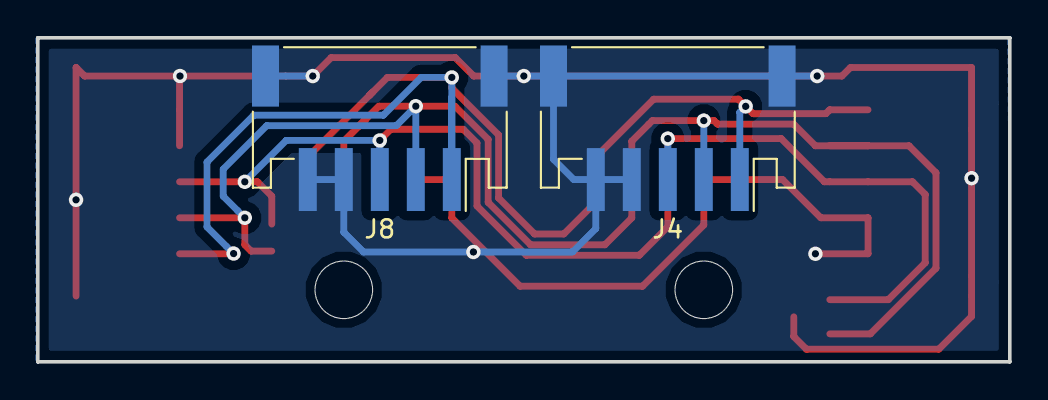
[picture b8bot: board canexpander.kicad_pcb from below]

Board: 2 copper layers, 54.0 x 18.0 mm, 10 parts (2 on the bottom side), 4 nets.

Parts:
D1: NUP2105LT1G; SOT-23
J1, J2, J3, J4, J5, J8: CocobotCAN; JST_PH_S5B-PH-SM4-TB_05x2.00mm_Angled
J6, J7: Conn_01x01; MountingHole_3.2mm_M3
R1: 120; R_0603

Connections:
GND: D1.3, J1.4, J1.5, J1.case, J2.4, J2.5, J2.case, J3.4, J3.5, J3.case, J4.4, J4.5, J4.case, J5.4, J5.5, J5.case, J8.4, J8.5, J8.case
unnamed: D1.1, J1.3, J2.3, J3.3, J4.3, J5.3, J8.3, R1.1
unnamed: D1.2, J1.2, J2.2, J3.2, J4.2, J5.2, J8.2, R1.2
unnamed: J1.1, J2.1, J3.1, J4.1, J5.1, J8.1
